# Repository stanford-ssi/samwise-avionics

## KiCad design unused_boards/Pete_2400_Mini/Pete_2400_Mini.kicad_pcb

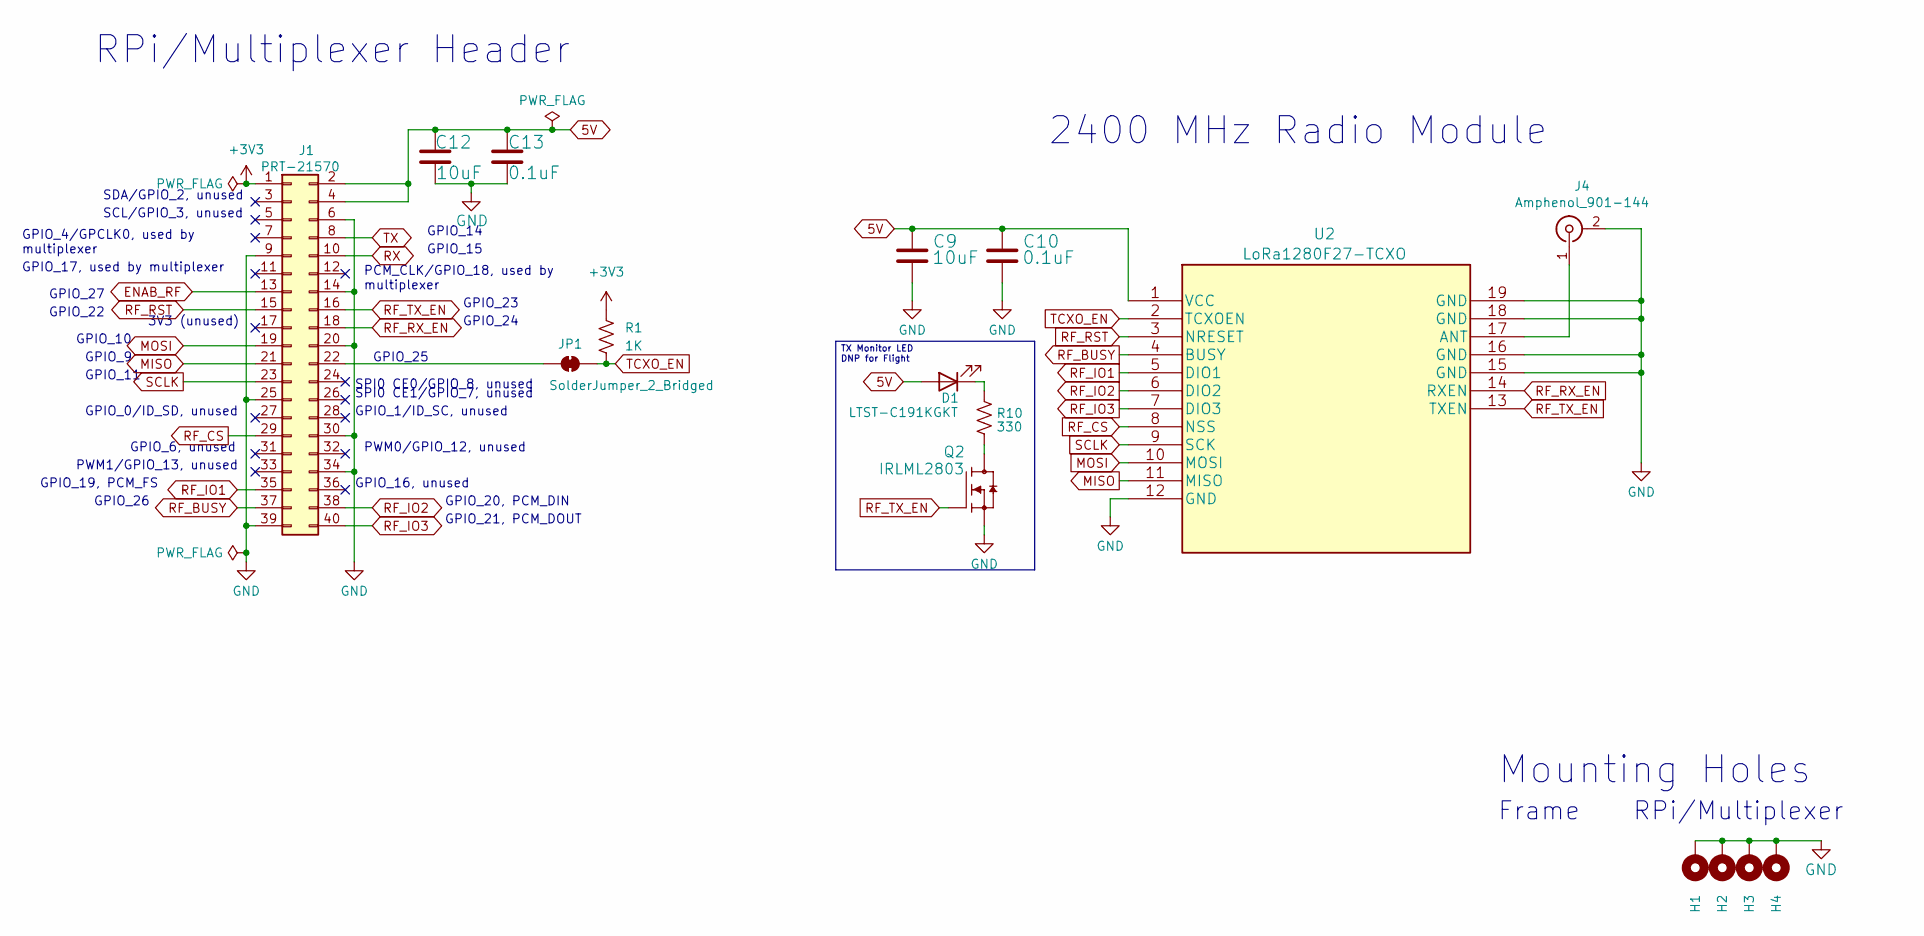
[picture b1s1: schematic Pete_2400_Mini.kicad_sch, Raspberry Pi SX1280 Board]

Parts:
C9, C12: 10uF; C_0603_1608Metric
C10, C13: 0.1uF; C_0603_1608Metric
D1: LTST-C191KGKT; LED_0603_1608Metric
H1, H2, H3, H4: MountingHole_Pad; MountingHole_2.7mm_M2.5_DIN965_Pad
J1: PRT-21570
J4: Amphenol_901-144; SMA_Amphenol_901-144_horizontal; Manufacturer_Part_Number 901-144
JP1: SolderJumper_2_Bridged; SolderJumper-2_P1.3mm_Bridged2Bar_RoundedPad1.0x1.5mm
Q2: IRLML2803; SOT-23; Manufacturer_Part_Number MMBT2222AT
R1: 1K; R_0603_1608Metric_Pad0.98x0.95mm_HandSolder
R10: 330; R_0603_1608Metric
U2: LoRa1280F27-TCXO; LORA128XF27

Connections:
5V: C9.1, C10.1, C12.1, C13.1, D1.2 (A), J1.2, J1.4, U2.1 (VCC)
+3V3: J1.1, R1.1
ENAB_RF: J1.13
GND: C9.2, C10.2, C12.2, C13.2, H1.1, H2.1, H3.1, H4.1, J1.6, J1.9, J1.14, J1.20, J1.25, J1.30, J1.34, J1.39, J4.2 (Ext), Q2.2 (S), U2.12 (GND), U2.15 (GND), U2.16 (GND), U2.18 (GND), U2.19 (GND)
MISO: J1.21, U2.11 (MISO)
MOSI: J1.19, U2.10 (MOSI)
unnamed: D1.1 (K), R10.1
unnamed: J1.22, JP1.1 (A)
unnamed: J4.1 (In), U2.17 (ANT)
unnamed: Q2.3 (D), R10.2
RF_BUSY: J1.37, U2.4 (BUSY)
RF_CS: J1.29, U2.8 (NSS)
RF_IO1: J1.35, U2.5 (DIO1)
RF_IO2: J1.38, U2.6 (DIO2)
RF_IO3: J1.40, U2.7 (DIO3)
RF_RST: J1.15, U2.3 (NRESET)
RF_RX_EN: J1.18, U2.14 (RXEN)
RF_TX_EN: J1.16, Q2.1 (G), U2.13 (TXEN)
RX: J1.10
SCLK: J1.23, U2.9 (SCK)
TCXO_EN: JP1.2 (B), R1.2, U2.2 (TCXOEN)
TX: J1.8

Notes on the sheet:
Mounting Holes
Frame
GPIO_0/ID_SD, unused
GPIO_21, PCM_DOUT
RPi/Multiplexer
RPi/Multiplexer Header
GPIO_1/ID_SC, unused
GPIO_19, PCM_FS
GPIO_15
GPIO_6, unused
GPIO_22
3V3 (unused)
GPIO_14
SDA/GPIO_2, unused
GPIO_11
GPIO_16, unused
GPIO_27
SCL/GPIO_3, unused
GPIO_10
TX Monitor LED DNP for Flight
PWM0/GPIO_12, unused
GPIO_20, PCM_DIN
GPIO_9
PCM_CLK/GPIO_18, used by multiplexer
PWM1/GPIO_13, unused
GPIO_25
2400 MHz Radio Module
SPI0 CE1/GPIO_7, unused
GPIO_23
GPIO_17, used by multiplexer
GPIO_4/GPCLK0, used by multiplexer
GPIO_24
SPI0 CE0/GPIO_8, unused
GPIO_26

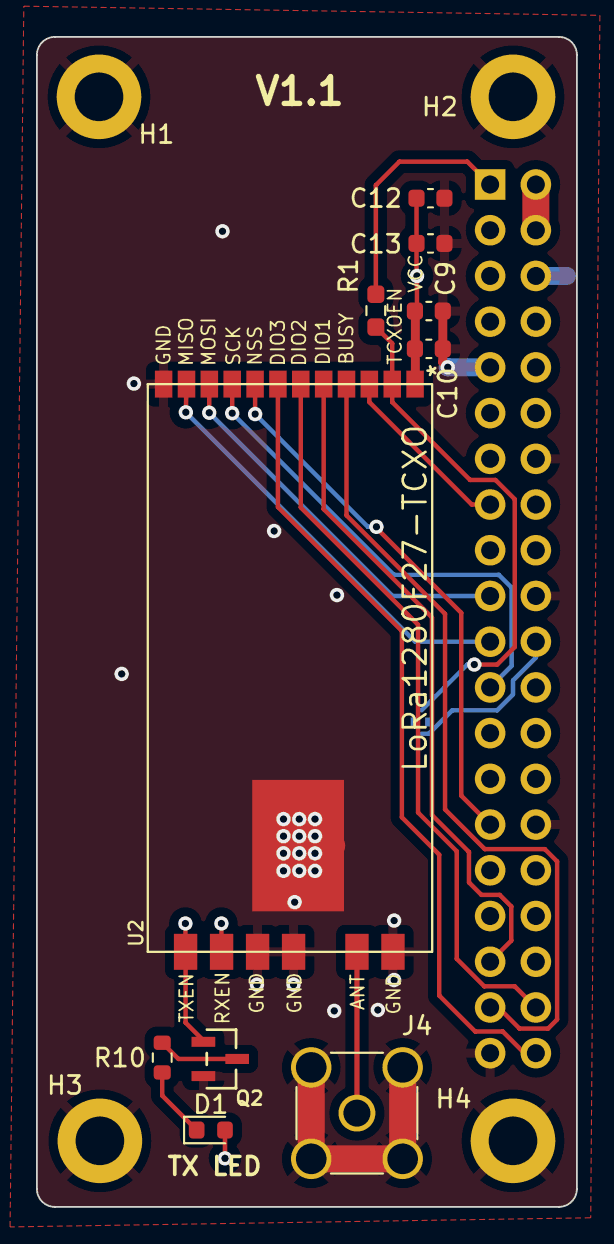
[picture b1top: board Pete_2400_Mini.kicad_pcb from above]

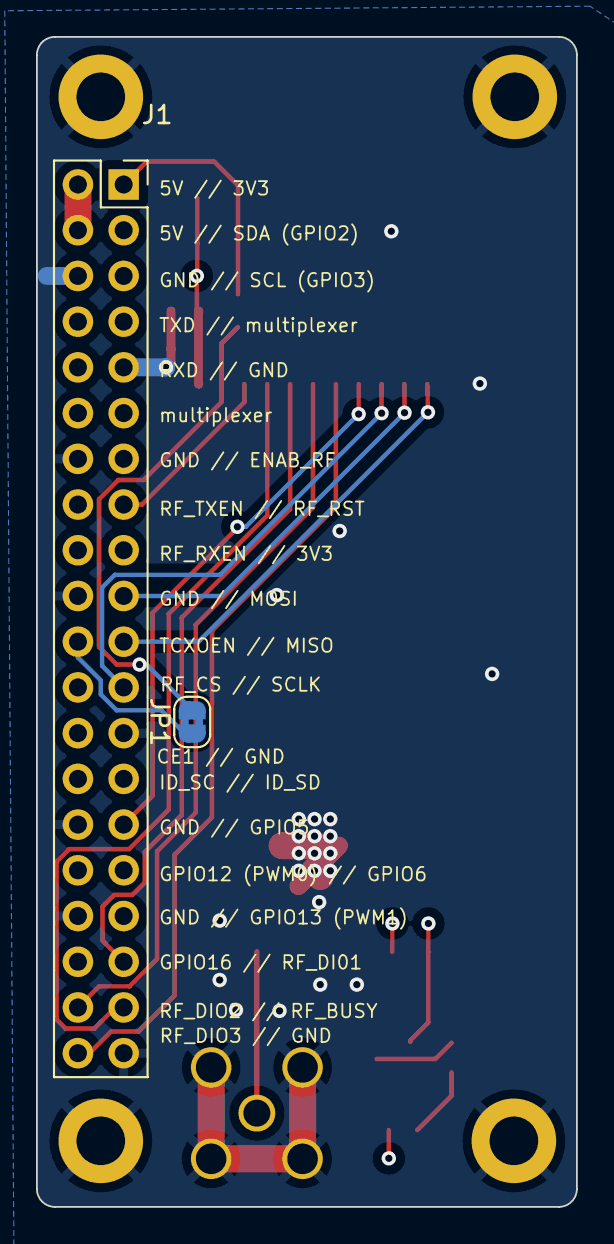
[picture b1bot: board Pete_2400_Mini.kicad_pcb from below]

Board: 4 copper layers, 30.0 x 65.0 mm, 16 parts (2 on the bottom side), 19 nets.

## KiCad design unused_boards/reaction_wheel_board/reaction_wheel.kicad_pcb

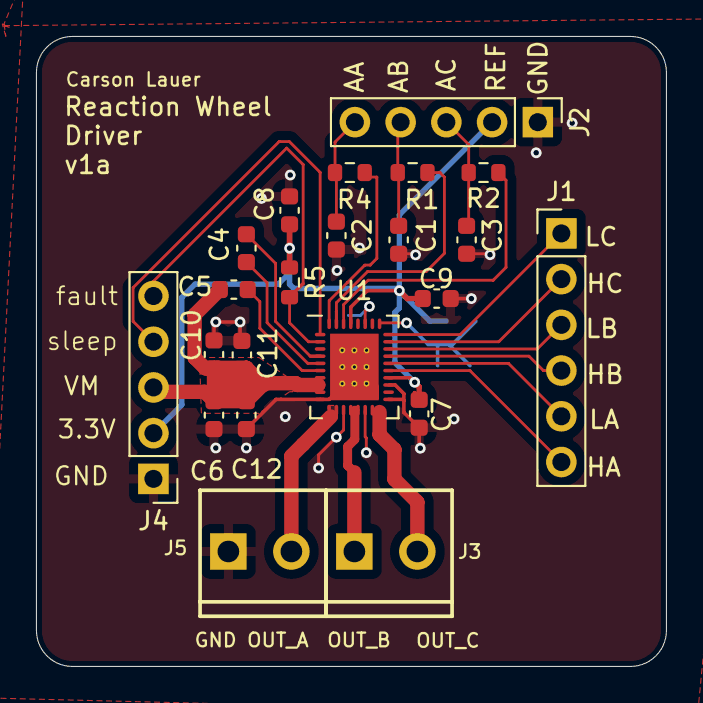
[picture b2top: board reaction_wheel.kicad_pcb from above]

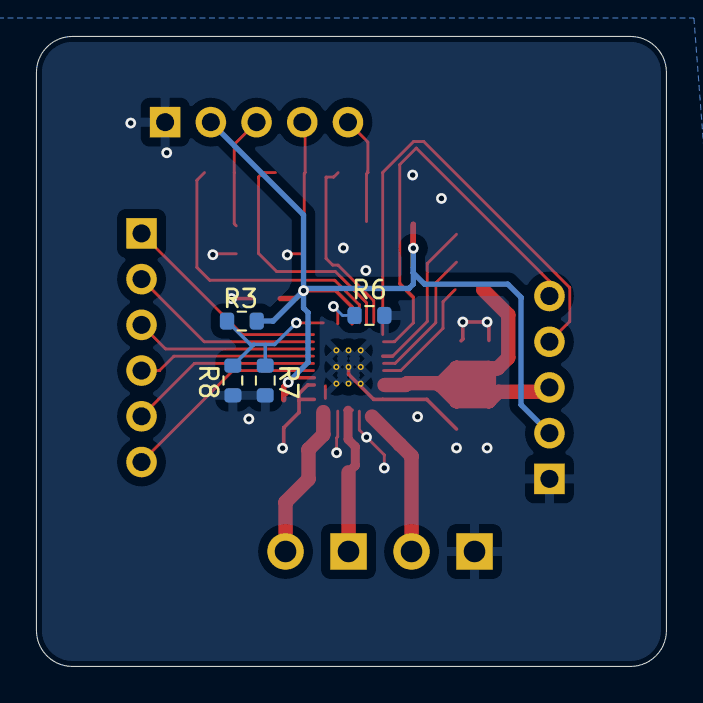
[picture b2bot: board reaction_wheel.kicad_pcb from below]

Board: 2 copper layers, 35.0 x 35.0 mm, 26 parts (4 on the bottom side), 25 nets.

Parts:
C1, C2, C3: 22pF; C_0603_1608Metric
C4: 47nF; C_0603_1608Metric
C5, C6, C8, C9, C11: 0.1μF; C_0603_1608Metric
C7: 4.7μF; C_0603_1608Metric
C10, C12: 10μF; C_0603_1608Metric
J1: PWM Pins; PinHeader_1x06_P2.54mm_Vertical
J2: Conn_01x05; PinHeader_1x05_P2.54mm_Vertical
J3, J5: Screw_Terminal_01x02; 1985807
J4: Power Pins; PinHeader_1x05_P2.54mm_Vertical
R1, R2, R4: 330; R_0603_1608Metric
R3, R7: 0R; R_0603_1608Metric
R5: 5.1kΩ; R_0603_1608Metric
R6, R8: 47k; R_0603_1608Metric
U1: DRV8317HREER; QFN-36_EP_4.6x5.4_Pitch0.4mm

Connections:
+3.3V: C7.1, C8.2, C9.2, J2.2, J4.2, R3.2, R5.1, U1.22 (AVDD), U1.33 (CSAREF)
+12V: C5.1, C6.2, C10.2, C11.2, C12.2, J4.3, U1.7 (VIN_AVDD), U1.8 (VM), U1.9 (VM)
/ADC_A: C2.1, J2.5, R4.2
/ADC_B: C1.1, J2.4, R1.2
/ADC_C: C3.1, J2.3, R2.2
/OUT_A: J5.2, U1.11 (OUTA), U1.12 (OUTA)
/OUT_B: J3.1, U1.14 (OUTB), U1.15 (OUTB)
/OUT_C: J3.2, U1.17 (OUTC), U1.18 (OUTC)
/PWM_H_A: J1.6, U1.23 (INHA)
/PWM_H_B: J1.4, U1.25 (INHB)
/PWM_H_C: J1.2, U1.27 (INHC)
/PWM_L_A: J1.5, U1.24 (INLA)
/PWM_L_B: J1.3, U1.26 (INLB)
/PWM_L_C: J1.1, U1.28 (INLC)
/fault: J4.5, R5.2, U1.2 (NFAULT)
/sleep: J4.4, U1.1 (NSLEEP)
GND: C1.2, C2.2, C3.2, C6.1, C7.2, C8.1, C9.1, C10.1, C11.1, C12.1, J2.1, J4.1, J5.1, R6.2, R7.1, R8.1, U1.10 (PGND), U1.13 (PGND), U1.16 (PGND), U1.19 (PGND), U1.21 (AGND), U1.37 (EPAD)
unnamed: C5.2, U1.6 (CP)
unnamed: C4.2, U1.5 (CPH)
unnamed: C4.1, U1.4 (CPL)
unnamed: R3.1, R7.2, R8.2, U1.29 (GAIN)
unnamed: R6.1, U1.31 (MODE)
unnamed: R4.1, U1.36 (SOA)
unnamed: R1.1, U1.35 (SOB)
unnamed: R2.1, U1.34 (SOC)
